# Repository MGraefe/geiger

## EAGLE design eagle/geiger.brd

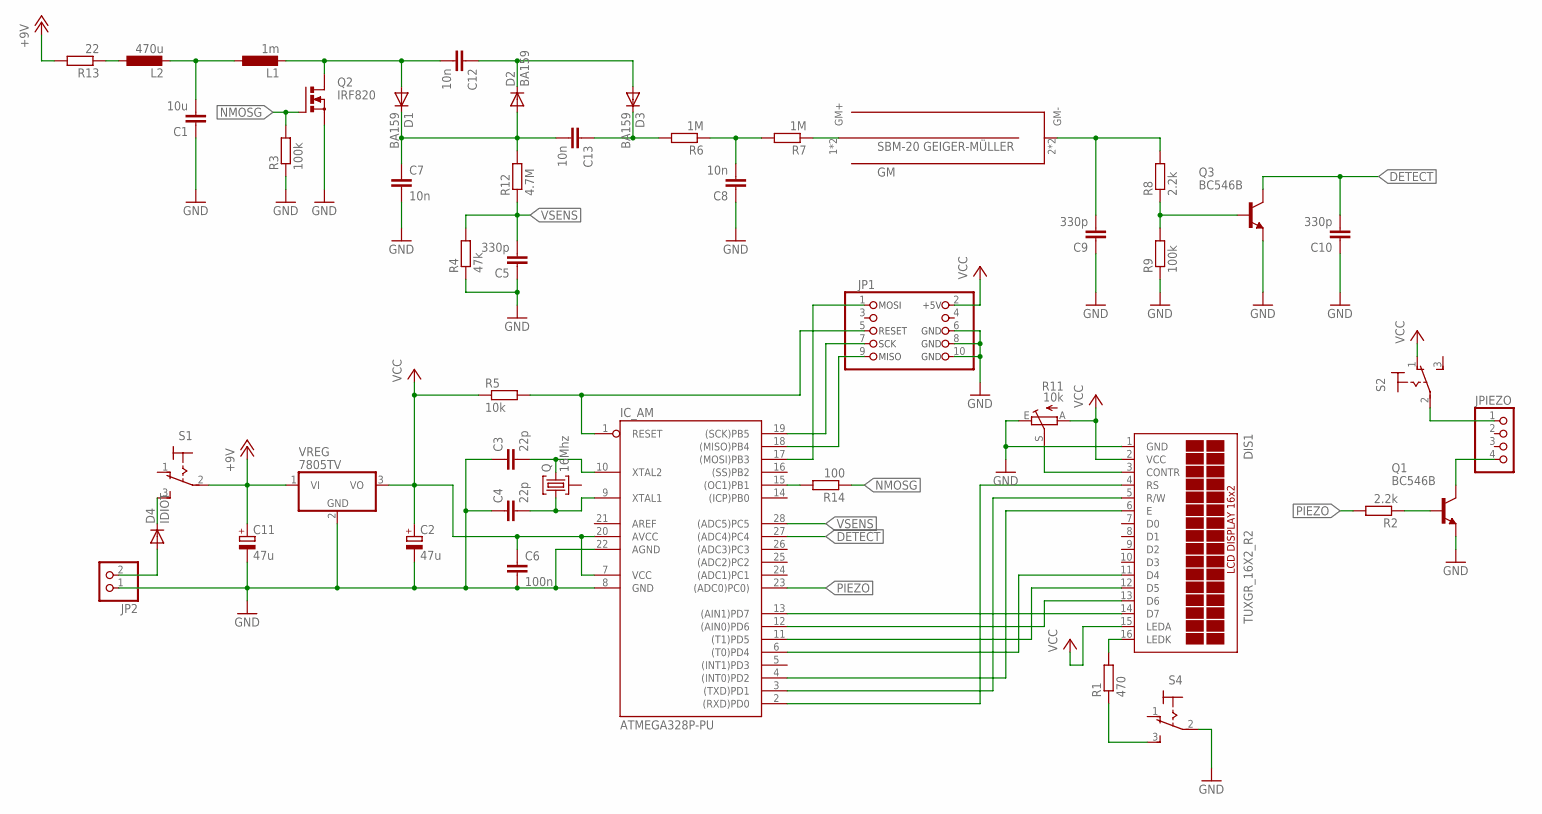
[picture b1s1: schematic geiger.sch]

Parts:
C1: 10u; C1206
C2, C11: 47u; E2,5-6
C3, C4: 22p; C0805
C5, C9, C10: 330p; C025-025X050
C6: 100n; C0805
C7, C8, C12, C13: 10n; C050-025X075
D1, D2, D3: BA159; DO41-7.6
D4: IDIOT; DO41-7.6
DIS1: TUXGR_16X2_R2
GM: SBM-20
IC_AM: ATMEGA328P-PU; DIL28-3
JP1: ISP10-M; 2X05
JP2: PINHD-1X2; 1X02
JPIEZO: PINHD-1X4; 1X04
L1: 1m; 6000-XXXX-RC
L2: 470u; 2200-12.7
Q: 16Mhz; HC49U
Q1, Q3: BC546B; TO92-EBC
Q2: IRF820; TO220BV
R1: 470; 0204/7
R2, R8: 2.2k; 0204/7
R3, R9: 100k; 0204/7
R4: 47k; 0204/7
R5: 10k; 0204/7
R6, R7: 1M; 0204/7
R11: 10k; CA6V
R12: 4.7M; 0204/7
R13: 22; 0204/7
R14: 100; R0805
S1, S2, S4: 320-916
VREG: 7805TV; TO220V

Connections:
+9V: C11.+, R13.2, S1.2, VREG.1 (VI)
DETECT: C10.2, IC_AM.27 ((ADC4)PC4), Q3.C
GND: C1.1, C2.-, C3.1, C4.1, C5.1, C6.2, C7.2, C8.1, C9.1, C10.1, C11.-, DIS1.1 (GND), IC_AM.8 (GND), IC_AM.22 (AGND), JP1.6, JP1.8, JP1.10, JP2.1, Q1.E, Q2.S, Q3.E, R3.1, R4.1, R9.1, R11.E, S4.2, VREG.2 (GND)
MISO: IC_AM.18 ((MISO)PB4), JP1.9
MOSI: IC_AM.17 ((MOSI)PB3), JP1.1
unnamed: DIS1.14 (D7), IC_AM.13 ((AIN1)PD7)
unnamed: DIS1.13 (D6), IC_AM.12 ((AIN0)PD6)
unnamed: DIS1.12 (D5), IC_AM.11 ((T1)PD5)
unnamed: DIS1.11 (D4), IC_AM.6 ((T0)PD4)
unnamed: DIS1.3 (CONTR), R11.S
unnamed: DIS1.6 (E), IC_AM.4 ((INT0)PD2)
unnamed: DIS1.5 (R/W), IC_AM.3 ((TXD)PD1)
unnamed: DIS1.4 (RS), IC_AM.2 ((RXD)PD0)
unnamed: C7.1, C13.2, D1.C, D2.A, R12.2
unnamed: DIS1.16 (LEDK), R1.2
unnamed: JPIEZO.4, Q1.C
unnamed: Q1.B, R2.1
unnamed: C8.2, R6.1, R7.2
unnamed: C9.2, GM.2 (GM-), GM.4 (GM-), R8.2
unnamed: GM.1 (GM+), GM.3 (GM+), R7.1
unnamed: D4.A, JP2.2
unnamed: Q3.B, R8.1, R9.2
unnamed: JPIEZO.1, S2.2
unnamed: R1.1, S4.3 (S)
unnamed: C12.1, D2.C, D3.A
unnamed: C1.2, L1.1, L2.2
unnamed: L2.1, R13.1
unnamed: IC_AM.15 ((OC1)PB1), R14.2
unnamed: C12.2, D1.A, L1.2, Q2.D
unnamed: C13.1, D3.C, R6.2
unnamed: D4.C, S1.3 (S)
NMOSG: Q2.G, R3.2, R14.1
PIEZO: IC_AM.23 ((ADC0)PC0)), R2.2
RESET: IC_AM.1 (RESET), JP1.5, R5.2
SCK: IC_AM.19 ((SCK)PB5), JP1.7
VCC: C2.+, C6.1, DIS1.2 (VCC), DIS1.15 (LEDA), IC_AM.7 (VCC), IC_AM.20 (AVCC), JP1.2, R5.1, R11.A, S2.1 (O), VREG.3 (VO)
VSENS: C5.2, IC_AM.28 ((ADC5)PC5), R4.2, R12.1
XTAL1: C4.2, IC_AM.9 (XTAL1), Q.1
XTAL2: C3.2, IC_AM.10 (XTAL2), Q.3

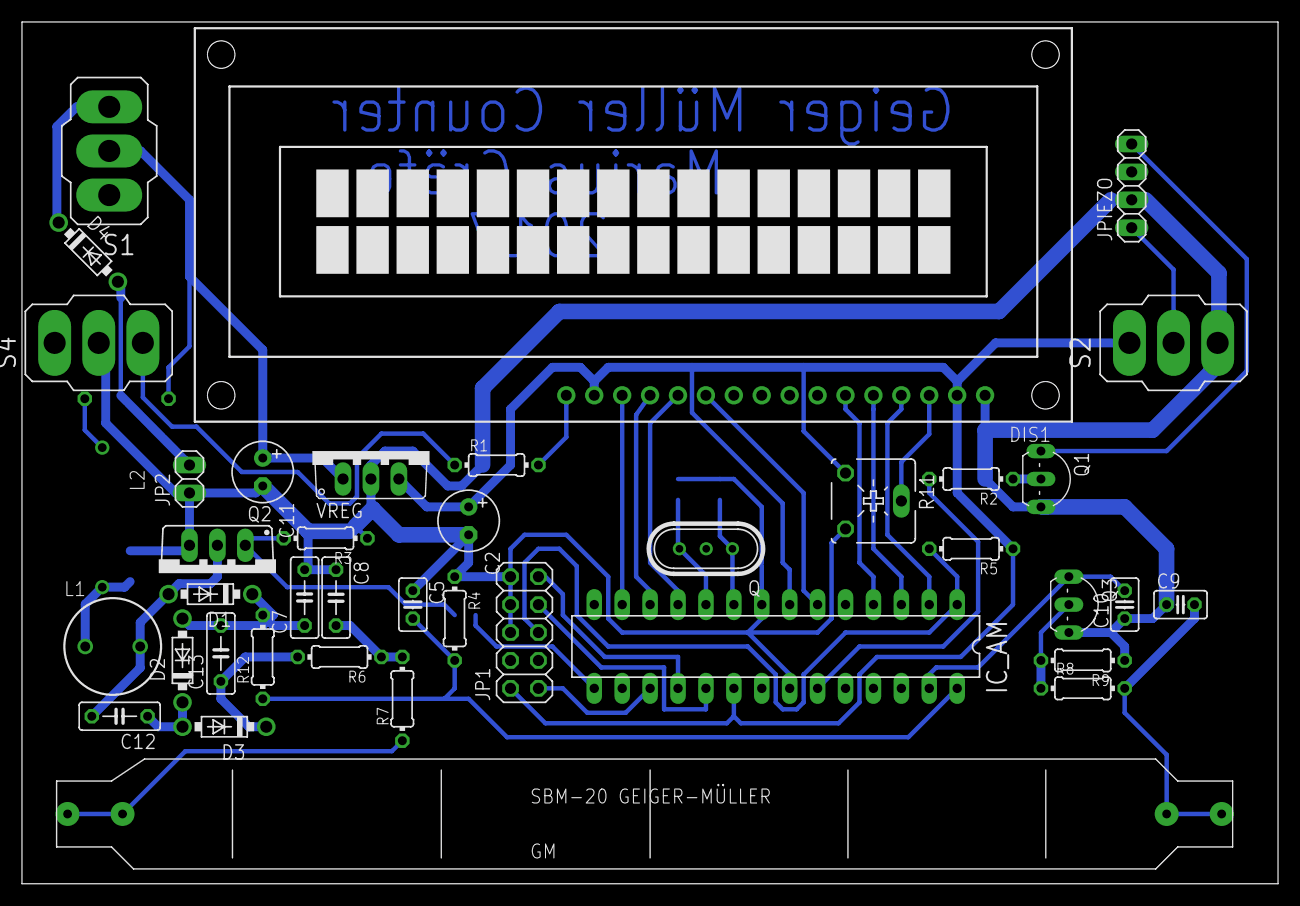
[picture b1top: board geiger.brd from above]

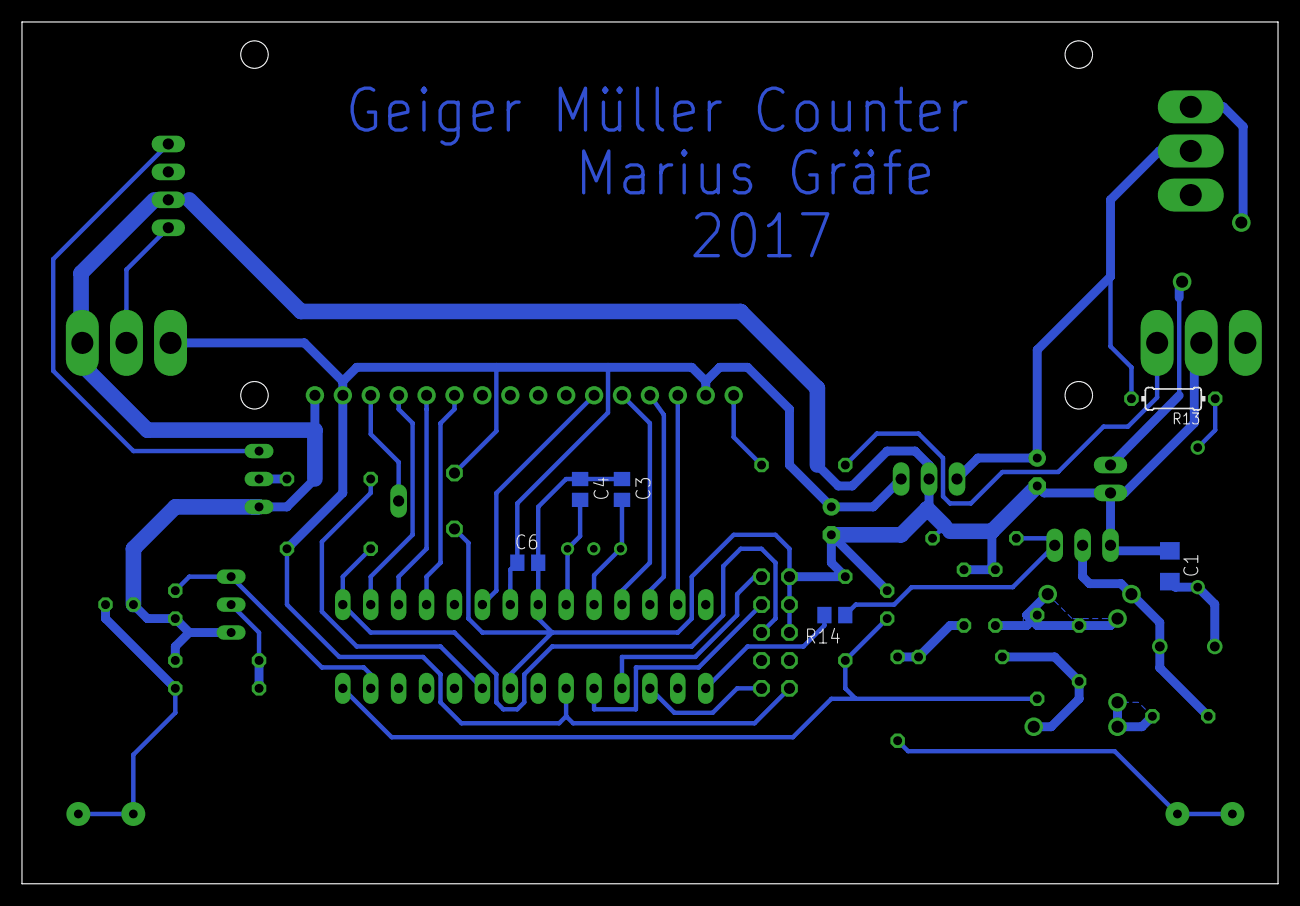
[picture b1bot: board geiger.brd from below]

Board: 2 copper layers, 114.3 x 78.4 mm, 46 parts (6 on the bottom side), 39 nets.

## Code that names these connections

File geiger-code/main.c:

#include <avr/io.h>
#include <avr/interrupt.h>
#include <util/delay.h>
#include <avr/sleep.h>
#include <avr/power.h>
#include <stdlib.h>
#include <string.h>

#include "lcd.h"


struct Lcd lcd_data;
struct Lcd *lcd = &lcd_data;
uint16_t g_pulses = 0;
uint16_t g_pulses_measurement = 0;
uint32_t g_millis = 0;
uint32_t g_cpm = 0;
uint16_t g_usv = 0;
uint8_t g_is_msv = 0;
uint32_t g_millis_measurement_started = 0;

#define PIN_PIEZO pin_create(PORT_C, 0)
#define PIN_NMOSG pin_create(PORT_B, 1)
#define PIN_DETECT pin_create(PORT_C, 4)
#define PIN_VSENSE pin_create(PORT_C, 5)

uint8_t g_piezo_beep = 0;
uint32_t g_timer1_cycles = 0;
uint32_t g_next_voltage_check = 0;
uint32_t g_next_lcd_update = 0;
uint32_t g_next_cpm_update = 0;
int16_t g_tube_voltage;
uint16_t g_tube_duty = 0;


// duty between 0 and UINT16_MAX
void set_mosfet_pwm(uint16_t duty)
{
	uint32_t duty32 = duty;
	OCR1A = (uint16_t)(duty32 * ICR1 / UINT16_MAX);
}


uint16_t read_analog(uint8_t i)
{
	uint8_t l, h;

	ADMUX = (1 << REFS0) | (i & 0x7);
	ADCSRA |= (1 << ADSC);
	while(ADCSRA & (1 << ADSC)) {};
	l = ADCL;
	h = ADCH;
	return (h << 8) | l;
}


void init()
{
	cli(); //stop interrupts
	
	pin_set_inout(PIN_PIEZO, 1);
	pin_set_inout(PIN_NMOSG, 1);
	pin_set_inout(PIN_DETECT, 0);
	pin_set_inout(PIN_VSENSE, 0);
	pin_set(PIN_DETECT, 1); // Enable internal pullup
	
	lcd_init(lcd, 1, pin_create(PORT_D, 0), pin_create(PORT_D, 1), pin_create(PORT_D, 2), 
		pin_create(PORT_D, 4), pin_create(PORT_D, 5), pin_create(PORT_D, 6), pin_create(PORT_D, 7), 0, 0, 0, 0);
	lcd_begin(lcd, 16, 2, LCD_5x8DOTS);
	
	// Pin change interrupt for handling geiger pulses
	PCICR |= (1 << PCIE1); // enable PCINT1 Interrupt Vector
	PCMSK1 |= (1 << PCINT12); // enable pin change interrupt on PCINT12 = PC4
	
	// Timer 2 used for timekeeping
	//ASSR |= (1 < AS2); // Use external clock
	TCCR2B |= 0x7; // Timer2 prescaler to 1024
	TIMSK2 |= (1 << TOIE2); // Enable Timer 2 interrupt on overflow
	#define CYCLES_PER_TIMER2 (1024L * 256L)
	
	// Set timer 1 for 10 bit non inverting fast pwm at 20 kHz for mosfet control
	ICR1 = F_CPU / 15000L; // 8 MHz / 20kHz = 800
	TCCR1A = (1 << COM1A1) | (1 << WGM11);
	TCCR1B = (1 << WGM12)  | (1 << WGM13) | (1 << CS10);
	//TIMSK1 = (1 << TOIE1);
	OCR1A = 0; // Output 0

	// Set ADC Converter enabled and 128 prescaler
	ADCSRA = (1 << ADEN) | (1 << ADPS2) | (1 << ADPS1) | (1 << ADPS0);

	// Power reduction
	PRR = (1 << PRTIM0) // Timer 0
		| (1 << PRTWI) // TWI (Two wire interface)
		| (1 << PRUSART0) // USART
		| (1 << PRSPI); // SPI

	sei(); //enable interrupts
}


// Geiger detect connected to PCINT12 -> triggers PCINT1_vect
ISR(PCINT1_vect)
{
	if ((PINC & (1 << PINC4)) == 0) // trigger on low flank
	{
		++g_pulses;
		++g_pulses_measurement;
		g_piezo_beep = 1;
	}
}


//Timer2 interrupt function (called every 1024 * 256 cycles = 32,768ms @ 8MHz)
#define CYLCES_PER_MS (F_CPU / 1000L)
ISR(TIMER2_OVF_vect)
{
	uint32_t millis;

	// Add cycles to g_timer1_cycles and subtract whole milliseconds from it
	g_timer1_cycles += CYCLES_PER_TIMER2;
	millis = g_timer1_cycles / CYLCES_PER_MS;
	g_timer1_cycles -= millis * CYLCES_PER_MS;
	g_millis += millis;
}


uint16_t clamp(uint16_t val, uint16_t min, uint16_t max)
{
	if (val < min)
		return min;
	if (val > max)
		return max;
	return val;
}


void voltageReg()
{
	uint16_t value;
	PRR &= ~(1 << PRADC); //enable adc in prr
	ADCSRA |= (1 << ADEN); //enable adc
	value = read_analog(5);
	ADCSRA &= ~(1 << ADEN); //disable adc
	PRR |= (1 << PRADC); //disable adc in prr

	// vcc is 5 volts and conversion factor is 1V sensed = 200V tube voltage, scale times 64 to get meaningful result
	g_tube_voltage = value * 64 / (uint16_t)((1.0f/1023.0f) * 5.0f * 200.0f * 64.0f + 0.5f);
	int16_t diff = 400 - g_tube_voltage;

	if (g_tube_voltage < 395 && g_tube_duty < (UINT16_MAX / 100 * 50))
		g_tube_duty += (UINT16_MAX / 1000) * clamp(diff / 8, 1, 20);
	else if (g_tube_voltage > 405 && g_tube_duty > (UINT16_MAX / 100 * 2))
		g_tube_duty -= (UINT16_MAX / 1000) * clamp(-diff / 8, 1, 20);
	set_mosfet_pwm(g_tube_duty);
}


/* A utility function to reverse a string  */
void reverse(char *str, int length)
{
	int start = 0;
	int end = length -1;
	char temp;
	while (start < end)
	{
		temp = str[start];
		str[start] = str[end];
		str[end] = temp;
		
		start++;
		end--;
	}
}

// Implementation of itoa()
int itoa_fill(int num, char* str, int base)
{
	int i = 0;
	uint8_t isNegative = 0;
	
	/* Handle 0 explicitely, otherwise empty string is printed for 0 */
	if (num == 0)
	{
		str[i++] = '0';
		return i;
	}
	
	// In standard itoa(), negative numbers are handled only with
	// base 10. Otherwise numbers are considered unsigned.
	if (num < 0 && base == 10)
	{
		isNegative = 1;
		num = -num;
	}
	
	// Process individual digits
	while (num != 0)
	{
		int rem = num % base;
		str[i++] = (rem > 9)? (rem-10) + 'a' : rem + '0';
		num = num / base;
	}
	
	// If number is negative, append '-'
	if (isNegative)
		str[i++] = '-';
		
	// Reverse the string
	reverse(str, i);
	
	return i;
}


void update_lcd()
{
	char line[32];
	memset(line, ' ', 16);

	itoa_fill(g_pulses, line, 10);

	int len = itoa_fill(g_tube_voltage, line + 3, 10);
	line[3 + len] = 'V';

	len = itoa_fill(g_tube_duty / (UINT16_MAX / 100), line + 7, 10);
	line[7 + len] = '%';

	len = itoa_fill(g_cpm, line + 11, 10);
	memcpy(line + 11 + len, "cpm", 3);

	line[16] = 0;
	lcd_home(lcd);
	lcd_write_str(lcd, line);

	memset(line, ' ', 16);
	itoa_fill(g_millis / 1000, line, 10);

	uint16_t wholeuSv = g_usv / 100;
	uint16_t commauSv = g_usv % 100;
	itoa_fill(wholeuSv, line + 5 + (wholeuSv < 10 ? 2 : wholeuSv < 100 ? 1 : 0), 10);
	line[8] = '.';
	if (commauSv < 10)
		line[9] = '0';
	itoa_fill(commauSv, line + 9 + (commauSv < 10 ? 1 : 0), 10);

	memcpy(line + 11, "uSv/h", 5);
	if (g_is_msv)
		line[11] = 'm';

	line[16] = 0;
	lcd_setCursor(lcd, 0, 1);
	lcd_write_str(lcd, line);
}

void loop()
{
	if (g_millis > g_next_cpm_update)
	{
		g_next_cpm_update += 2000; // Update every 2 seconds
		uint32_t elapsed = g_millis - g_millis_measurement_started;
		if (g_pulses_measurement > 100 || elapsed > 5)
		{
			float cpm = (float)g_pulses_measurement * 60.0f / (elapsed * 0.001f);
			g_cpm = (uint16_t)(cpm + 0.5f);
			float usv = cpm * 0.006315f; // Factor for SBM-20
			g_is_msv = 0;
			if (usv > 99.99f)
			{
				usv *= 0.001f;
				g_is_msv = 1;
			}
			g_usv = (uint16_t)(usv * 100.0f);
		}

		if (g_pulses_measurement > 100)
		{
			g_millis_measurement_started = g_millis;
			cli();
			g_pulses_measurement = 0;
			sei();
		}
	}
	
	if (g_millis > g_next_lcd_update)
	{
		g_next_lcd_update = g_millis + 200;
		update_lcd();
	}

	if (g_piezo_beep)
	{
		pin_set(PIN_PIEZO, 1);
		_delay_us(100);
		pin_set(PIN_PIEZO, 0);
		g_piezo_beep = 0;
	}

	if (g_millis > g_next_voltage_check)
	{
		voltageReg();
		g_next_voltage_check = g_millis + 100; // more relaxed afterwards
	}

	set_sleep_mode(SLEEP_MODE_IDLE);
	sleep_mode();
	//_delay_ms(1);
}


int main(void)
{
	_delay_ms(200);
	init();
	
    while (1) 
    {
		loop();
    }
}

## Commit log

2017-01-20 Added sensing
2017-01-20 Changed 16 to 8 MHz
2017-02-04 Done more work
2017-02-05 More work
2017-02-05 Added burn batch files
2017-02-07 Added cpm calculation, output and power reduction
2017-02-07 Improvements
2017-02-08 New calculation method
2018-11-13 Added schematics and board layout
